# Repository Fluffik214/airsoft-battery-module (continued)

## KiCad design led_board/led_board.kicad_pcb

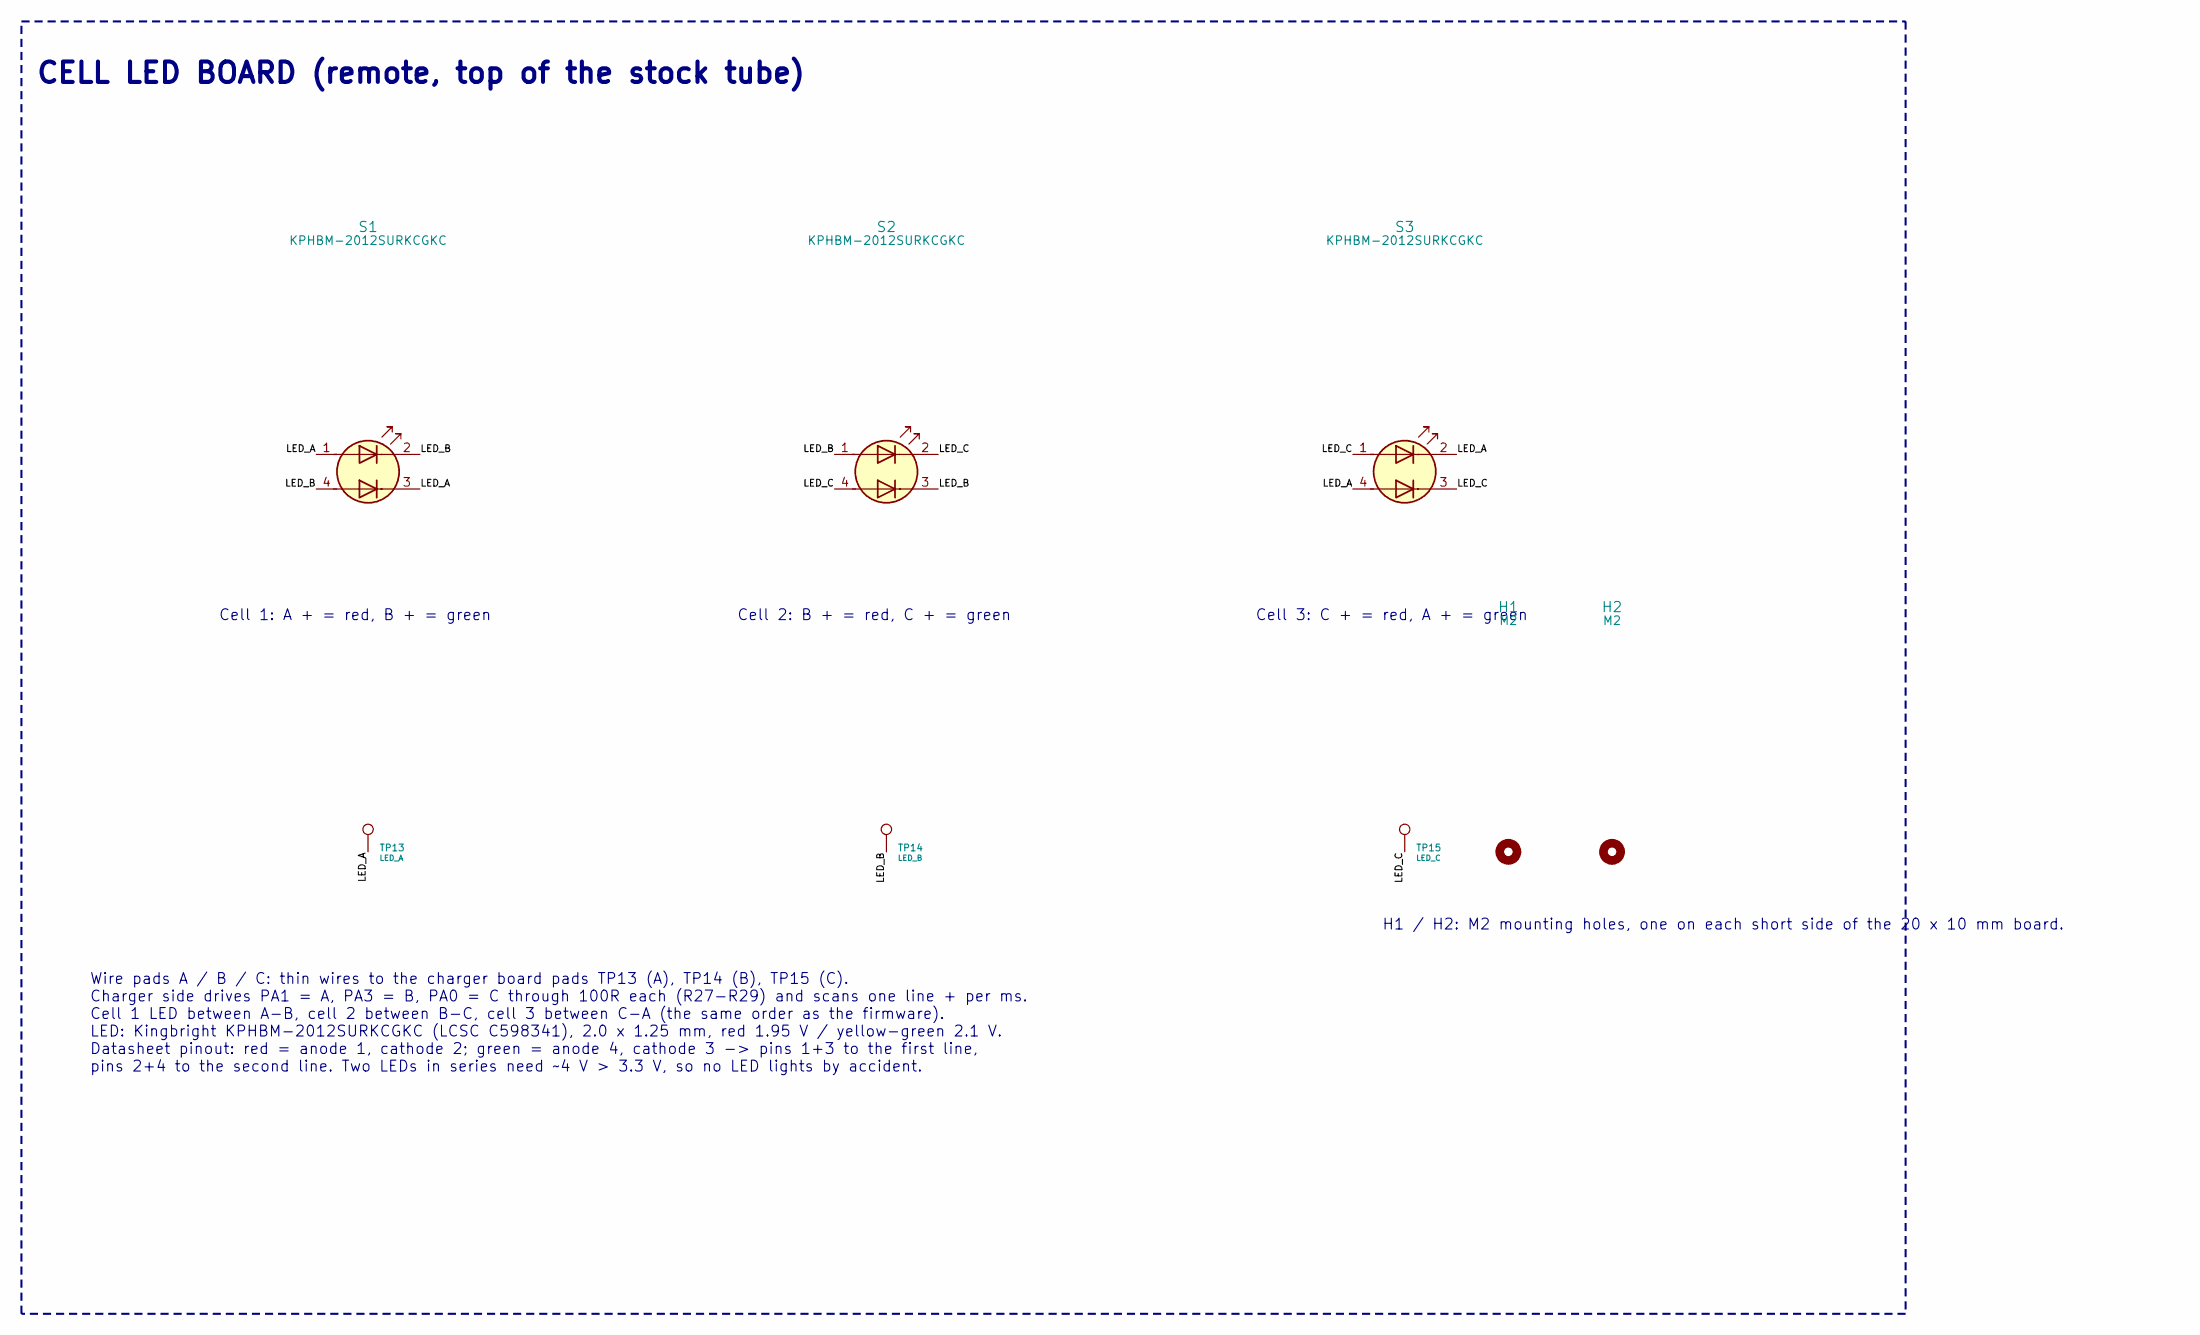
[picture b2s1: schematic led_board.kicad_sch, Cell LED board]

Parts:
H1, H2: M2; MountingHole_2.2mm_M2
S1, S2, S3: KPHBM-2012SURKCGKC; LED_Kingbright_APHBM2012_2x1.25mm; MPN Kingbright KPHBM-2012SURKCGKC; LCSC C598341
TP13: LED_A; TestPoint_Pad_D1.5mm
TP14: LED_B; TestPoint_Pad_D1.5mm
TP15: LED_C; TestPoint_Pad_D1.5mm

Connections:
/LED_A: S1.1 (A1), S1.3 (K2), S3.2 (K1), S3.4 (A2), TP13.1
/LED_B: S1.2 (K1), S1.4 (A2), S2.1 (A1), S2.3 (K2), TP14.1
/LED_C: S2.2 (K1), S2.4 (A2), S3.1 (A1), S3.3 (K2), TP15.1

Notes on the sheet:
CELL LED BOARD (remote, top of the stock tube)
Cell 1: A + = red, B + = green
Cell 2: B + = red, C + = green
Cell 3: C + = red, A + = green
H1 / H2: M2 mounting holes, one on each short side of the 20 x 10 mm board.
Wire pads A / B / C: thin wires to the charger board pads TP13 (A), TP14 (B), TP15 (C). Charger side drives PA1 = A, PA3 = B, PA0 = C through 100R each (R27-R29) and scans one line + per ms. Cell 1 LED between A-B, cell 2 between B-C, cell 3 between C-A (the same order as the firmware). LED: Kingbr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

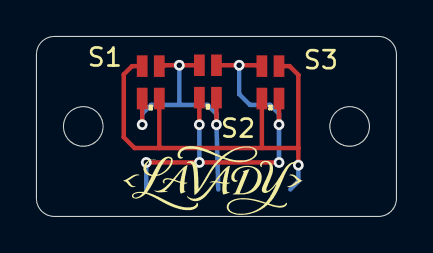
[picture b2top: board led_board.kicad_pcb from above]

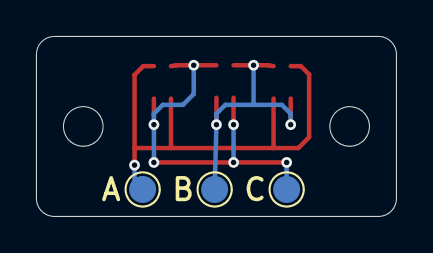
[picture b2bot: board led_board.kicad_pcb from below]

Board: 2 copper layers, 20.0 x 10.0 mm, 9 parts (3 on the bottom side), 3 nets.

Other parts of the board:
LOGO*: LOGO; LAVADY logo 10x3.8mm

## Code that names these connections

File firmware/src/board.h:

// Airsoft PD charger - board pin map (STM32F042F6P6, TSSOP-20), matches schematic Rev A
#pragma once

// GPIOA
#define PIN_LED_C       0   // PA0  led : cell LED line C (charlieplexed, 100R R29 -> pad TP15)
#define PIN_LED_A       1   // PA1  led : cell LED line A (100R R27 -> pad TP13)
#define PIN_CHG_EN      2   // PA2  out : high -> Q1 pulls BQ25798 /CE low -> charging allowed
#define PIN_LED_B       3   // PA3  led : cell LED line B (100R R28 -> pad TP14)
#define PIN_BMS_BOOT    4   // PA4  out : pulse high ~5 ms to boot BQ76920 from SHIP (via 1k into TS1)
#define PIN_VBUS_SENSE  5   // PA5  adc : VBUS / 11 (100k / 10k divider) -> ADC_IN5
#define PIN_LED         6   // PA6  pwm : green status LED (TIM3_CH1, AF1)
#define PIN_PWR_HOLD    7   // PA7  out : high keeps the MCU powered from the pack after USB is unplugged
// PA11/PA12 = USB DM/DP (pins 17/18, remapped), PA13/PA14 = SWD
// GPIOB
#define PIN_FAST_N      1   // PB1  in  : JP2 solder jumper to GND (internal pull-up). open = slow charge, bridged = fast
// GPIOF
#define PIN_I2C_SDA     0   // PF0 I2C1_SDA (AF1)
#define PIN_I2C_SCL     1   // PF1 I2C1_SCL (AF1)

#define VBUS_DIV        11u      // (100k + 10k) / 10k
#define VBUS_MAX_MV     17000u   // above this USB voltage charging is cut immediately (CH224K should give 15 V)
#define I2C_ADDR_BQ25798 0x6B
#define I2C_ADDR_BQ76920 0x08    // BQ7692003: 3.3 V REGOUT, address 0x08, CRC enabled

#define FW_VERSION      "1.0.0"
#define HW_VERSION      "RevB"   // RevB: pack on the balance plug only (no Deans pads), cell LED pads

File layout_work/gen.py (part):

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                      x + 5.08, y, {'1': '+3V3', '2': 'MCU_BOOT0'}, ref='JP1')
next(r); x, y = next(r); place('Jumper:SolderJumper_2_Open', 'JP', 'FAST CHARGE', 'Jumper:SolderJumper-2_P1.3mm_Open_RoundedPad1.0x1.5mm',
                      x + 5.08, y, {'1': 'FAST_CHG_N', '2': 'GND'}, ref='JP2',
                      props={'Note': 'open (default) = slow charge, bridged = fast charge. PB1 internal pull-up.'})
text("PF0/PF1 = I2C1 SDA/SCL (AF1). PA11/PA12 remapped onto pins 17/18 for USB (SYSCFG PA11_PA12_RMP).\n"
     "PA1/PA3/PA0 = charlieplexed cell LEDs A/B/C (pads TP13-15). Charger /INT, CH224K PG and BMS ALERT are not\n"
     "wired to the MCU (firmware polls I2C). PA2 CHG_EN, PA4 BMS boot, PA5 VBUS/11 ADC, PA6 LED, PA7 PWR_HOLD.\n"
     "PB1 = FAST_CHG_N (JP2 to GND, internal pull-up): open = slow charge (default), bridged = fast charge.\n"
     "Bridge JP1 + plug USB = ST ROM DFU bootloader. Backup: ST-Link on test pads TP5 SWDIO, TP6 SWCLK, TP7 3V3, TP8 GND.",
     204, 237, 1.4)

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                      {'1': 'PACK_P', '2': 'BAT_P'}, ref='F1',
                      props={'MPN': 'AEM F1206SB2500V032TM (LCSC C310999), 2.5A fast, 50A breaking'})
text("The pack connects ONLY through the JST-XH balance plug J2 (no Deans / main-lead pads).\n"
     "Charge current: J2 pin 1 (pack +) -> F1 2.5A fast -> BAT_P (charger), return via J2 pin 4 (GND).\n"
     "J2 pin order follows the pack's plug: its black wire lands on header pin 4 (checked on the real pack).\n"
     "F1 protects the thin balance wires: a board short would otherwise burn them inside the stock.\n"
     "Max charge 1.4 A (JP2 bridged). JST-XH is rated 3 A on AWG22; keep 26 AWG leads at <= ~2 A.\n"
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
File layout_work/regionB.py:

# =====================================================================================
# REGION B : MCU (U6 rot 90), decoupling/straps, MCU power path (U5, D3, Q2, Q3)
# (exec'd from route.py: b, pad, VIA_S, W_SIG in scope)
# =====================================================================================
P = lambda r, n: pad(r, n)

# ---- top edge of U6: VDD16 + C31, GND15
xv, yv = P('U6', 16); xg, yg = P('U6', 15)
xc1, yc1 = P('C31', 1); xc2, yc2 = P('C31', 2)
b.track('+3V3', [(xc1, yc1), (xv, yv - 0.6)], 0.25)
b.track('GND', [(xg, yg - 0.6), (xg, 101.4)], 0.25)
b.via('GND', xg, 101.4, **VIA_S)
b.track('GND', [(xg, 101.4), (xc2 + 0.25, yc2), (xc2, yc2)], 0.25)

# ---- +3V3 / VDDA hop under the IC body (bottom layer)
b.track('+3V3', [(xv, yv + 0.6), (xv, 105.2)], 0.25)
b.via('+3V3', xv, 105.2, **VIA_S)
x5, y5 = P('U6', 5)
b.track('+3V3', [(x5, y5 - 0.6), (x5, 108.0)], 0.25)
b.via('+3V3', x5, 108.0, **VIA_S)
b.track('+3V3', [(xv, 105.2), (x5, 108.0)], 0.3, B)

# ---- PD_PG: CH224K PG -> R3 pull-up only (no longer wired to the MCU)
x10, y10 = P('U1', 10); x7, y7 = P('U6', 7)
xr, yr = P('R3', 2); b.track('PD_PG', [(x10, y10), (xr - 0.5, y10), (xr, y10 - 0.5), (xr, yr)], W_SIG)
# ---- CLED_A (pin 7, PA1): under the MCU body, west, down to a via, bottom layer to the LED pads (regionG)
CLA_V = (123.2, 108.8)
b.track('CLED_A', [(x7, y7 - 0.6), (x7, 107.0), (x7 - 0.5, 106.5), (CLA_V[0] + 0.5, 106.5), (CLA_V[0], 107.0), CLA_V], W_SIG)
b.via('CLED_A', *CLA_V, **VIA_S)
xr, yr = P('R3', 1); b.track('+3V3', [(xr, yr), (123.4, yr)], 0.25); b.via('+3V3', 123.4, yr, **VIA_S)
b.track('+3V3', [(123.4, yr), (123.4, 108.0)], 0.3, B)        # joins the +3V3 bottom run at y 108

# ---- bottom-row fan-out
x, y = P('U6', 1)          # BOOT0 -> R21 (pull-down) + JP1 (DFU bridge)
xj, yj = P('JP1', 2); xr21, yr21 = P('R21', 1)
b.track('MCU_BOOT0', [(x, y + 0.6), (x, 112.8), (x - 0.5, 113.3), (xj, 113.3), (xj, yj)], W_SIG)
b.track('MCU_BOOT0', [(xr21, 113.3), (xr21, yr21)], W_SIG)
xg2, yg2 = P('R21', 2); b.track('GND', [(xg2, yg2), (xg2, yg2 + 0.9)], 0.3); b.via('GND', xg2, yg2 + 0.9, **VIA_S)
xa, ya = P('JP1', 1); b.track('+3V3', [(xa, ya), (xa, ya + 1.0)], 0.3); b.via('+3V3', xa, ya + 1.0, **VIA_S)
b.track('+3V3', [(x5, 108.0), (122.9, 108.0), (122.4, 108.5), (122.4, ya + 0.5), (xa, ya + 1.0)], 0.3, B)

x, y = P('U6', 4)          # NRST -> C34 directly below
xc, yc = P('C34', 1); b.track('MCU_NRST', [(x, y + 0.6), (xc, yc)], W_SIG)
xc, yc = P('C34', 2); b.track('GND', [(xc, yc), (xc, 112.55)], 0.3); b.via('GND', xc, 112.55, **VIA_S)
x, y = P('U6', 5)          # VDDA -> C32
xc, yc = P('C32', 1); b.track('+3V3', [(x, y + 0.6), (xc, yc)], 0.25)
xc, yc = P('C32', 2); b.track('GND', [(xc, yc), (127.35, 115.45), (127.35, 116.1)], 0.3); b.via('GND', 127.35, 116.1, **VIA_S)

# bus: top verticals down to a staggered via row, then bottom-layer lanes east along the bottom edge
LANE = {'+3V3': 116.8, 'BMS_BOOT': 117.35, 'CHG_EN': 117.9, 'I2C_SCL': 118.45, 'I2C_SDA': 119.0}
# (packed up so the bus stays >= 0.3 mm clear of the strap notches in the bottom edge, which reach y 119.5)
# local 45-deg steps per lane: [(x_from, x_to, y at the stepped level)]
# the I2C pair drops back to its old levels where it tees into the charger (U3 pins are only 0.4 mm apart)
JOGS = {'I2C_SCL': [(162.8, 164.4, 119.55)], 'I2C_SDA': [(162.8, 165.0, 120.1)]}
def lane_y(net, x):
    for x1, x2, jy in JOGS.get(net, []):
        if x1 <= x <= x2: return jy
    return LANE[net]
def lane_pts(net, x0):
    ly = LANE[net]; pts = [(x0, ly)]
    for x1, x2, jy in JOGS.get(net, []):
        d = abs(ly - jy)
        pts += [(x1 - d, ly), (x1, jy), (x2, jy), (x2 + d, ly)]
    return pts + [(LEND[net], ly)]
FAN = [('I2C_SDA', 2, 115.6), ('I2C_SCL', 3, 116.0),       # via rows sit below the back text (glyphs y 113.0-115.25)
       ('CHG_EN', 8, 116.0), ('BMS_BOOT', 10, 116.0)]
LEND = {'I2C_SDA': 182.0, 'I2C_SCL': 182.6, 'CHG_INT_N': 171.2, 'CHG_EN': 159.05, 'BMS_ALERT': 184.5,
        'BMS_BOOT': 183.3, '+3V3': 184.28}
for net, pin, vy in FAN:
    x, y = P('U6', pin)
    b.track(net, [(x, y + 0.6), (x, vy)], W_SIG)
    b.via(net, x, vy, **VIA_S)
    ly = LANE[net]
    b.track(net, [(x, vy), (x, ly - 0.4)] + lane_pts(net, x + 0.4), W_SIG, B)

# ---- top lanes from the top-right pins: PWR_HOLD 101.1, LED 101.85, VBUS_SENSE 102.55
x13, y13 = P('U6', 13); x12, y12 = P('U6', 12); x11, y11 = P('U6', 11)
xr22, yr22 = P('R22', 2)
b.track('VBUS_SENSE', [(x11, y11 - 0.6), (x11, 102.55), (xr22 - 0.45, 102.55), (xr22, 103.0), (xr22, yr22)], W_SIG)
xa, ya = P('R23', 1); xb, yb = P('C35', 1)
b.track('VBUS_SENSE', [(xr22, 103.25), (xr22 + 0.65, 103.9), (xr22 + 0.65, ya - 0.45), (xa, ya)], W_SIG)   # down past R22 to the divider below SL1
b.track('VBUS_SENSE', [(xa, ya), (xb, yb)], W_SIG)
xa, ya = P('R23', 2); xb, yb = P('C35', 2)
b.track('GND', [(xa, ya), (xb, yb)], 0.3); b.track('GND', [(xa, ya), (xa + 0.85, ya)], 0.3); b.via('GND', xa + 0.85, ya, **VIA_S)
xr, yr = P('R22', 1)
b.track('VBUS', [(xr, 118.9), (xr, yr)], 0.3)       # VBUS up from the lane to the divider
# LED
xr, yr = P('R26', 1)
b.track('LED_STATUS', [(x12, y12 - 0.6), (x12, 101.85), (xr - (yr - 101.85), 101.85), (xr, yr)], W_SIG)
xa, ya = P('R26', 2); xb, yb = P('D4', 2); b.track('LED_G_A', [(xa, ya), (xb, yb)], W_SIG)
xb, yb = P('D4', 1); b.track('GND', [(xb, yb), (xb, yb + 0.95)], 0.3); b.via('GND', xb, yb + 0.95, **VIA_S)
# PWR_HOLD -> Q3 gate, R20 pull-down
xg, yg = P('Q3', 1); xr, yr = P('R20', 1)
# PWR_HOLD drops to y 101.95 past the strap notch at x 137.1 (notch reaches y 101.5); LED row sits below at 102.7
b.track('PWR_HOLD', [(x13, y13 - 0.6), (x13, 100.95), (133.4, 100.95), (134.4, 101.95), (xg - 1.0, 101.95), (xg, yg)], W_SIG)
b.track('PWR_HOLD', [(xr, yr), (xr, yg), (xg, yg)], W_SIG)
xr, yr = P('R20', 2); b.track('GND', [(xr, yr), (xr, yr + 0.8)], 0.3); b.via('GND', xr, yr + 0.8, **VIA_S)
xs, ys = P('Q3', 2); b.track('GND', [(xs, ys), (xs, ys + 0.9)], 0.3); b.via('GND', xs, ys + 0.9, **VIA_S)
# WAKE_G: Q3 drain -> short bottom hop -> Q2 gate ; R19 (1M to BAT_P)
xd, yd = P('Q3', 3); xq, yq = P('Q2', 1); xr, yr = P('R19', 2)
w1 = (xd + 1.0, yd)                      # just outside the drain pad (no via-in-pad)
b.track('WAKE_G', [(xd, yd), w1], W_SIG); b.via('WAKE_G', *w1, **VIA_S)
b.track('WAKE_G', [w1, (w1[0], yr), (xr, yr)], W_SIG)
w2 = (xq - 0.65, 101.95)
b.track('WAKE_G', [w1, (w1[0] + 0.6, w1[1] - 0.6), (w2[0], 102.3 - 0.0), w2], W_SIG, B)
b.via('WAKE_G', *w2, **VIA_S)
b.track('WAKE_G', [w2, (xq, yq)], W_SIG)
# BAT_P thin feed along the top edge from the charger -> Q2 source + R19
xs, ys = P('Q2', 2); xr, yr = P('R19', 1)
bx = (w1[0] + w2[0]) / 2
b.track('BAT_P', [(177.3, 101.1), (176.6, 101.1), (175.6, 102.1), (171.4, 102.1), (170.4, 101.1), (bx + 0.4, 101.1),   # dips past the notch at x 173.5
                   (bx, 101.5), (bx, ys), (xs, ys)], 0.3)
b.track('BAT_P', [(bx, ys), (bx, yr), (xr, yr)], 0.3)
# WAKE_RAIL: Q2 drain -> D3 pin 2
xd, yd = P('Q2', 3); x2, y2 = P('D3', 2)
b.track('WAKE_RAIL', [(xd, yd), (x2, yd), (x2, y2)], 0.3)
# VIN_LDO: D3 pin 3 -> U5 VI, C29
x3, y3 = P('D3', 3); xi, yi = P('U5', 1); xc, yc = P('C29', 1)
b.track('VIN_LDO', [(x3, y3), (xi + 0.5, y3), (xi, yi)], 0.4)
b.track('VIN_LDO', [(x3, y3), (xc, y3), (xc, yc)], 0.4)
xc, yc = P('C29', 2); b.track('GND', [(xc, yc), (xc - 1.3, yc)], 0.4); b.via('GND', xc - 1.3, yc)   # beside C29, clear of the back text
# VBUS into D3 pin 1 from the lane
x1, y1 = P('D3', 1)
b.track('VBUS', [(x1 + 0.7, 118.8), (x1 + 0.7, y1 + 0.5), (x1 + 0.2, y1), (x1, y1)], 0.5)
# LDO output -> C30/C33 -> via -> bottom: west to the MCU, east as the +3V3 bus lane
xo, yo = P('U5', 2); xa1, ya1 = P('C30', 1); xa2, ya2 = P('C33', 1)
vA = (143.6, 107.5)
b.track('+3V3', [(xo, yo), (xa1, yo), (xa1, ya1)], 0.4)
b.track('+3V3', [(vA[0], yo), vA], 0.4)
b.track('+3V3', [(xa1, ya1), (xa2, ya1), (xa2, ya2)], 0.4)
b.via('+3V3', *vA)
b.track('+3V3', [vA, (vA[0] - 0.5, 108.0), (x5, 108.0)], 0.4, B)
b.track('+3V3', [vA, (vA[0], LANE['+3V3'] - 0.4)] + lane_pts('+3V3', vA[0] + 0.4), 0.3, B)
for c in ('C30', 'C33'):
    xc, yc = P(c, 2); b.track('GND', [(xc, yc), (xc, yc + 0.9)], 0.3); b.via('GND', xc, yc + 0.9, **VIA_S)
xg, yg = P('U5', 3); b.track('GND', [(xg, yg), (xg, yg + 0.9)], 0.4); b.via('GND', xg, yg + 0.9)

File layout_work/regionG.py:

# =====================================================================================
# REGION G : cell-LED wire pads TP13 LED_A, TP14 LED_B, TP15 LED_C (near the USB-C) with their
#            100R series resistors R27..R29 ; JP2 fast-charge jumper (back, under U6).
# Lanes run west along the free top-layer strip between the MCU via row and the VBUS lane.
# =====================================================================================
P = lambda r, n: pad(r, n)
def via_s(net, x, y): b.via(net, x, y, **VIA_S)
# resistors (rot 90): pad 1 (MCU side) at the bottom, pad 2 (wire pad side) at the top
for r, t, n in (('R27', 'TP13', 'LED_A'), ('R28', 'TP14', 'LED_B'), ('R29', 'TP15', 'LED_C')):
    b.track(n, [P(r, 2), P(t, 1)], 0.25)
# CLED_C: pin 6 (PA0) straight down, west on the upper lane into R29
x6, y6 = P('U6', 6); r29 = P('R29', 1)
b.track('CLED_C', [(x6, y6 + 0.6), (x6, r29[1] - 0.0), r29], W_SIG)
# CLED_B: pin 9 (PA3) down past the lane above, west on the lower lane, up into R28
x9, y9 = P('U6', 9); r28 = P('R28', 1)
LB = 117.6
b.track('CLED_B', [(x9, y9 + 0.6), (x9, LB), (r28[0], LB), r28], W_SIG)
# CLED_A: from the via under the MCU (regionB) down the bottom layer, west under the lanes, up at R27
r27 = P('R27', 1); LA = 118.1
b.track('CLED_A', [CLA_V, (CLA_V[0], LA - 0.5), (CLA_V[0] - 0.5, LA), (r27[0], LA)], W_SIG, B)
via_s('CLED_A', r27[0], LA)
b.track('CLED_A', [(r27[0], LA), r27], W_SIG)
# silk letters above the wire pads
for t, s in (('TP13', 'A'), ('TP14', 'B'), ('TP15', 'C')):
    x, y = P(t, 1); b.text(s, x, y - 1.85, pcbnew.F_SilkS, 0.8)

# JP2 (FAST CHARGE, back, under U6): pin 14 (PB1) -> via -> bottom -> JP2 pad 1 ; pad 2 sits in the GND pour
x14, y14 = P('U6', 14); j1 = P('JP2', 1)
b.track('FAST_CHG_N', [(x14, y14 + 0.6), (x14, 105.2)], W_SIG)
b.via('FAST_CHG_N', x14, 105.2, **VIA_S)
b.track('FAST_CHG_N', [(x14, 105.2), j1], W_SIG, B)

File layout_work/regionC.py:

# =====================================================================================
# REGION C : BQ25798 charger, U3 rot 0 @ (163.0, 112.4)
# TI layout guideline: 0.1uF PMID/SYS caps on the pins, SW1/SW2 via under the IC to the
# inductor on the bottom layer, BTST caps on the bottom at those vias.
# Bottom-side parts: C5, C6 (BTST), C19 (REGN), R5 (BATP).
# Bottom bus lanes occupy y 116.65..120.2 -> no vias there except lane taps.
# =====================================================================================
P = lambda r, n: pad(r, n)
def via_s(net, x, y): b.via(net, x, y, **VIA_S)

# ---------------- top-row power pins: C10 (PMID 100n) / C16 (SYS 100n), GND bar to pin 27
x29, y29 = P('U3', 29); x27, y27 = P('U3', 27); x25, y25 = P('U3', 25)
x28, y28 = P('U3', 28); x26, y26 = P('U3', 26)
c10p, c10g = P('C10', 1), P('C10', 2)
c16p, c16g = P('C16', 1), P('C16', 2)
b.track('PMID', [(x29, y29 - 0.3), (x29, c10p[1])], 0.2)
b.track('SYS', [(x25, y25 - 0.3), (x25, c16p[1])], 0.2)
b.track('GND', [(x27, y27 - 0.3), (x27, c10g[1])], 0.2)
b.track('GND', [c10g, c16g], 0.4)
b.track('GND', [(x27, c10g[1]), (x27, 106.75)], 0.4)
for vy in (107.6, 106.75):
    b.via('GND', x27, vy)

# ---------------- SW1 / SW2: pins -> vias under the IC -> bottom -> vias in the inductor pads
l1a, l1b = P('L1', 1), P('L1', 2)
SW1V = [(162.25, 111.95), (162.25, 112.75)]
SW2V = [(163.75, 111.95), (163.75, 112.75)]
b.track('SW1', [(x28, y28 + 0.3), (x28, 111.5), SW1V[0], SW1V[1]], 0.25)
b.track('SW2', [(x26, y26 + 0.3), (x26, 111.5), SW2V[0], SW2V[1]], 0.25)
for v in SW1V: b.via('SW1', *v)
for v in SW2V: b.via('SW2', *v)
# inductor vias sit just ABOVE the pads (not in-pad) so they can't wick solder away from the joint
VY = 102.55
L1V1 = [(l1a[0] - 0.4, VY), (l1a[0] + 0.4, VY)]
L1V2 = [(l1b[0] - 0.4, VY), (l1b[0] + 0.4, VY)]
for v in L1V1: b.via('SW1', *v)
for v in L1V2: b.via('SW2', *v)
for (va, vb), lp, net in ((L1V1, l1a, 'SW1'), (L1V2, l1b, 'SW2')):
    b.track(net, [va, vb], 0.6)                                  # top: via pair joined
    b.track(net, [(lp[0], VY), (lp[0], lp[1] - 1.2)], 0.8)       # top: into the pad
    b.track(net, [va, vb], 0.6, B)
b.track('SW1', [SW1V[1], SW1V[0], (162.25, 110.0), (l1a[0], 109.4), (l1a[0], VY)], 0.8, B)
b.track('SW2', [SW2V[1], SW2V[0], (163.75, 110.0), (l1b[0], 109.4), (l1b[0], VY)], 0.8, B)

# ---------------- left edge: VBUS sense pins, BTST1, REGN, STAT
x4, y4 = P('U3', 4); x5, y5 = P('U3', 5); x8, y8 = P('U3', 8); x9, y9 = P('U3', 9); x1, y1 = P('U3', 1)
bt1 = (159.85, 112.2); rg1 = (160.15, 113.05); st1 = (160.2, 110.5)
b.track('BTST1', [(x4 - 0.2, y4), (160.1, y4), bt1], W_SIG); via_s('BTST1', *bt1)
b.track('REGN', [(x5 - 0.2, y5), (160.4, y5), rg1], W_SIG); via_s('REGN', *rg1)
b.track('CHG_STAT', [(161.0, 110.8), (160.65, 110.8), (160.4, 110.55), st1], W_SIG); via_s('CHG_STAT', *st1)
b.track('VBUS', [(x8 - 0.2, y8), (160.4, y8 + 0.2), (158.4, y8 + 0.2)], 0.2)
b.track('VBUS', [(160.95, 114.0), (159.9, 114.0), (159.7, y8 + 0.2)], 0.2)
c4a, c4b = P('C4', 1), P('C4', 2)
b.track('GND', [c4b, (c4b[0], 110.6)], 0.3); b.via('GND', c4b[0], 110.6, **VIA_S)
c5a, c5b = P('C5', 1), P('C5', 2)            # bottom: BTST1 cap
b.track('BTST1', [bt1, c5a], 0.25, B); b.track('SW1', [c5b, SW1V[0]], 0.4, B)

# ---------------- REGN network on the bottom: rg1 -> C19 -> R10 via, -> right side, -> LED (left)
c19a = P('C19', 1)
r10v = (161.0, 115.55)
b.track('REGN', [rg1, (rg1[0], 113.6), c19a], 0.3, B)
b.track('REGN', [c19a, (c19a[0], r10v[1] - 0.4), r10v], 0.3, B); via_s('REGN', *r10v)
r10a, r10b = P('R10', 1), P('R10', 2)
b.track('REGN', [r10v, r10a], W_SIG)
rg2 = (165.95, 114.05)
b.track('REGN', [c19a, (165.95, c19a[1]), rg2], 0.3, B); via_s('REGN', *rg2)
rg3 = (151.65, 112.7)
b.track('REGN', [rg1, (rg1[0] - 0.4, 113.4), (152.0, 113.4), rg3], 0.25, B); via_s('REGN', *rg3)

# ---------------- STAT LED (D2 + R8) left of the charger
d2k, d2a = P('D2', 1), P('D2', 2); r8a, r8b = P('R8', 1), P('R8', 2)
st2 = (151.9, d2k[1])
b.track('CHG_STAT', [st1, (159.8, 109.9), (152.2, 109.9), (st2[0], 110.2), st2], 0.25, B); via_s('CHG_STAT', *st2)
b.track('CHG_STAT', [st2, d2k], W_SIG)
b.track('CHG_LED_A', [d2a, (d2a[0], r8b[1] - 0.5), r8b], W_SIG)
b.track('REGN', [rg3, r8a], W_SIG)

# ---------------- right edge stack: INT (far right), PROG, BTST2, BATP, REGN(ILIM), TS
x21, y21 = P('U3', 21); x20, y20 = P('U3', 20); x19, y19 = P('U3', 19)
x18, y18 = P('U3', 18); x17, y17 = P('U3', 17); x16, y16 = P('U3', 16)
INT_X = 171.2
r9a, r9b = P('R9', 1), P('R9', 2)          # INT pull-up to +3V3 (INT no longer goes to the MCU)
b.track('CHG_INT_N', [(x21 + 0.2, y21), (INT_X, y21), (INT_X, r9b[1]), r9b], W_SIG)
y3 = lane_y('+3V3', r9a[0])
b.track('+3V3', [r9a, (r9a[0], y3)], 0.25); via_s('+3V3', r9a[0], y3)
r4a = P('R4', 1)
b.track('CHG_PROG', [(x20 + 0.2, y20), (r4a[0], y20), r4a], W_SIG)
bt2 = (167.2, 113.25)
b.track('BTST2', [(x19 + 0.2, y19), (166.75, y19), bt2], W_SIG); via_s('BTST2', *bt2)
c6a, c6b = P('C6', 1), P('C6', 2)          # bottom: BTST2 cap
b.track('BTST2', [bt2, c6a], 0.25, B); b.track('SW2', [c6b, SW2V[1]], 0.4, B)
bpv = (166.65, 113.9)
b.track('CHG_BATP', [(x18 + 0.2, y18), (166.4, y18), bpv], W_SIG); via_s('CHG_BATP', *bpv)
r5a, r5b = P('R5', 1), P('R5', 2)          # bottom: BATP 100R, Kelvin into the BAT copper
b.track('CHG_BATP', [bpv, r5a], 0.25, B)
b.track('BAT_P', [r5b, (169.6, r5b[1]), (169.6, 111.4)], 0.3, B); via_s('BAT_P', 169.6, 111.4)
b.track('REGN', [(x17 + 0.2, y17), (165.5, y17), rg2], W_SIG)
r6a, r6b = P('R6', 1), P('R6', 2)          # TS bias: REGN -> R6 -> TS ; R7 + NTC TH1 to GND
b.track('REGN', [rg2, (rg2[0], r6a[1] - 0.5), r6a], W_SIG)
b.track('CHG_TS', [(164.4, 114.45), (164.4, r6b[1] - 0.4), r6b], W_SIG)
r7a = P('R7', 1); th1a = P('TH1', 1)
b.track('CHG_TS', [r6b, r7a], W_SIG)
b.track('CHG_TS', [r7a, th1a], W_SIG)

# ---------------- bottom edge: GND10/11 via under the IC, CE -> Q1 + R10, SCL/SDA down to taps
x10, y10 = P('U3', 10); x11, y11 = P('U3', 11); x13, y13 = P('U3', 13)
x14, y14 = P('U3', 14); x15, y15 = P('U3', 15)
gv = (162.3, 113.62)
b.track('GND', [(x10, y10 - 0.3), gv, (x11, y11 - 0.3)], 0.2); via_s('GND', *gv)
ys = lane_y('I2C_SCL', x14); b.track('I2C_SCL', [(x14, y14 + 0.3), (x14, ys)], W_SIG); via_s('I2C_SCL', x14, ys)
b.track('I2C_SDA', [(x15, y15 + 0.3), (x15, 118.8), (x15 + 0.5, 119.3), (x15 + 0.5, lane_y('I2C_SDA', x15 + 0.5))], W_SIG); via_s('I2C_SDA', x15 + 0.5, lane_y('I2C_SDA', x15 + 0.5))
qd, qg = P('Q1', 3), P('Q1', 1)
b.track('CHG_CE_N', [(x13, y13 + 0.3), (x13, qd[1] - 0.5), (x13 - 0.5, qd[1]), qd], W_SIG)
b.track('CHG_CE_N', [r10b, (x13, r10b[1])], W_SIG)
cg = (159.05, LANE['CHG_EN'])
b.track('CHG_EN', [qg, (cg[0], qg[1]), cg], W_SIG); via_s('CHG_EN', *cg)
r11a, r11b = P('R11', 1), P('R11', 2)     # CHG_EN pull-down sits at the MCU pin
x8m, y8m = P('U6', 8)
b.track('CHG_EN', [r11a, (x8m, r11a[1])], W_SIG)
b.track('GND', [r11b, (r11b[0], 111.3)], 0.3); via_s('GND', r11b[0], 111.3)

# ---------------- SDRV cap
x24, y24 = P('U3', 24); c20a, c20b = P('C20', 1), P('C20', 2)
b.track('CHG_SDRV', [(x24 + 0.3, y24), c20a], W_SIG)
b.track('GND', [c20b, (c20b[0] + 0.75, c20b[1])], 0.3); via_s('GND', c20b[0] + 0.75, c20b[1])

# ---------------- bulk cap GND vias (PMID/SYS/VBUS/BAT)
for c in ('C7', 'C8', 'C9', 'C11', 'C12', 'C13', 'C14', 'C15'):
    xg, yg = P(c, 2); b.track('GND', [(xg, yg), (xg, yg - 0.95)], 0.5); b.via('GND', xg, yg - 0.95)
xg, yg = P('C2', 2); b.track('GND', [(xg, yg), (xg, yg - 0.8)], 0.5); b.via('GND', xg, yg - 0.8)
xg, yg = P('C3', 2); b.track('GND', [(xg, yg), (xg - 0.9, yg)], 0.5); b.via('GND', xg - 0.9, yg)
for c in ('C17', 'C18'):
    xg, yg = P(c, 2); b.track('GND', [(xg, yg), (xg + 0.95, yg)], 0.5); b.via('GND', xg + 0.95, yg)

# VBUS lane from the USB end into the VBUS input copper
b.track('VBUS', [(154.0, 119.3), (156.6, 119.3), (157.8, 118.1)], 1.0)
# ---------------- power copper (top)
b.zone('PMID', F, [(152.6, 108.55), (161.6, 108.55), (161.6, 109.05), (162.45, 109.05), (162.45, 110.0),
                   (161.85, 110.0), (161.85, 109.85), (152.6, 109.85)], priority=5, name='PMID')
b.zone('SYS', F, [(163.55, 109.05), (164.4, 109.05), (164.4, 108.55), (176.3, 108.55), (176.3, 109.85),
                  (164.15, 109.85), (164.15, 110.0), (163.55, 110.0)], priority=5, name='SYS')
b.zone('VBUS', F, [(157.0, 111.0), (161.1, 111.0), (161.1, 111.75), (160.1, 111.75), (158.6, 113.25),
                   (158.6, 118.8), (152.0, 118.8), (152.0, 119.8), (157.0, 119.8)], priority=5, name='VBUS_IN')
b.zone('BAT_P', F, [(165.0, 111.05), (176.6, 111.05), (176.6, 100.6), (178.1, 100.6), (178.1, 111.7),
                    (165.0, 111.7)], priority=5, name='BAT_OUT')
